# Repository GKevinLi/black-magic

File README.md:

# Black Magic: A Brushless DC Motor Driver

This is a custom 4S 20A Sensorless BLDC Motor Driver designed for drone motor operation. I haven't had time to make the drone itself because I spent all my time designing this custom PCB instead. Still worth it though.

Features a DRV8323 motor driver chip along with a STM32 microcontroller. Supports full sensorless brushless DC motor operation through PWM input along with current sensing. 

It's called Black Magic because, let's be honest here, I'm messing around with powers beyond my comprehension. I'll be lucky if this thing doesn't blow up the first time I try to plug it in, although I've done my best to make sure that doesn't happen. 20A is still way too much current for someone like me to be playing around with.

This took way longer to make than the other one.... i think its obvious why

## Features
- DRV8323 Motor Controller chip
- STM32 Microcontroller
- USB-C port for programming
- PWM Input
- BEMF Detection through a virtual neutral point
- Current Sensing capabilities
- Voltage Regulator for 3.3v power

## BOM

| Item  | Usage | Source  | Price | Quantity | LCSC ID|
| ----| ----|----|----|----|----|
| 100 uf electrolytic capaciator | Bulk Capacitance | JLCPCB | $4.65 | 20 | C7272127 |
| 10 uf capaciator | Capacitance | JLCPCB | $0.08 | 15 | C19702 |
| 3.3 nf capaciator | Capacitance | JLCPCB | $0.10 | 20 | C26404 |
| 100 nf capaciator | Capacitance | JLCPCB | $0.04 | 40 | C1525 |
| 22 uf capaciator | Bulk Capacitance | JLCPCB | $5.25 | 25 | C5189846 |
| 22 uf capaciator (0603 footprint) | Capacitance | JLCPCB | $0.09 | 10 | C59461 |
| 2.2 uf capaciator | Capacitance | JLCPCB | $0.01 | 5 | C12530 |
| 1 uf capaciator | Capacitance | JLCPCB | $0.02 | 5 | C52923 |
| 47 nf capaciator | Capacitance | JLCPCB | $0.04 | 20 | C272875 |
| Schottky Diode | Preventing reverse current | JLCPCB | $0.10 | 10 | C191023 |
| Red LED | Indication | JLCPCB | $0.03 | 5 | C2286 |
| USB C Receptacle | Programming + Power | JLCPCB | $0.30 | 6 | C2927038 |
| MOSFET | Motor Control | JLCPCB | $8.06 | 30 | C201632 |
| 10 ohm resistor | Resistance | JLCPCB | $0.02 | 30 | C25077 |
| 33k ohm resistor | Resistance | JLCPCB | $0.02 | 30 | C25779 |
| 68k ohm resistor | Resistance | JLCPCB | $0.01 | 30 | C36871 |
| 22k ohm resistor | Resistance | JLCPCB | $0.01 | 5 | C25768 |
| 100k ohm resistor | Resistance | JLCPCB | $0.01 | 5 | C25741 |
| 10k ohm resistor | Resistance | JLCPCB | $0.01 | 20 | C25741 |
| 5.1k ohm resistor | Resistance | JLCPCB | $0.01 | 15 | C25905 |
| 0.01 ohm shunt resistor | Shunt Resistance | JLCPCB | $1.05 | 19 | C393070 |
| 4.7k ohm resistor | Resistance | JLCPCB | $0.01 | 5 | C25900 |
| Button | Button | JLCPCB | $0.42 | 10 | C720477 |
| STM32 | Microcontroller | JLCPCB | $15.86 | 5 | C529355 |
| USBLC6 | USB Data Protector | JLCPCB | $0.96 | 5 | C15999 |
| TLV76133 | Voltage Regulator | JLCPCB | $1.10 | 5 | C7527500 |
| DRV8323 | Motor driver | JLCPCB | $13.29| 5 | C7527500 |
| TPS82130 | Buck Converter | JLCPCB | $6.35 | 5 | C473914 |

Total JLCPCB Assmebly Cost: $73.70

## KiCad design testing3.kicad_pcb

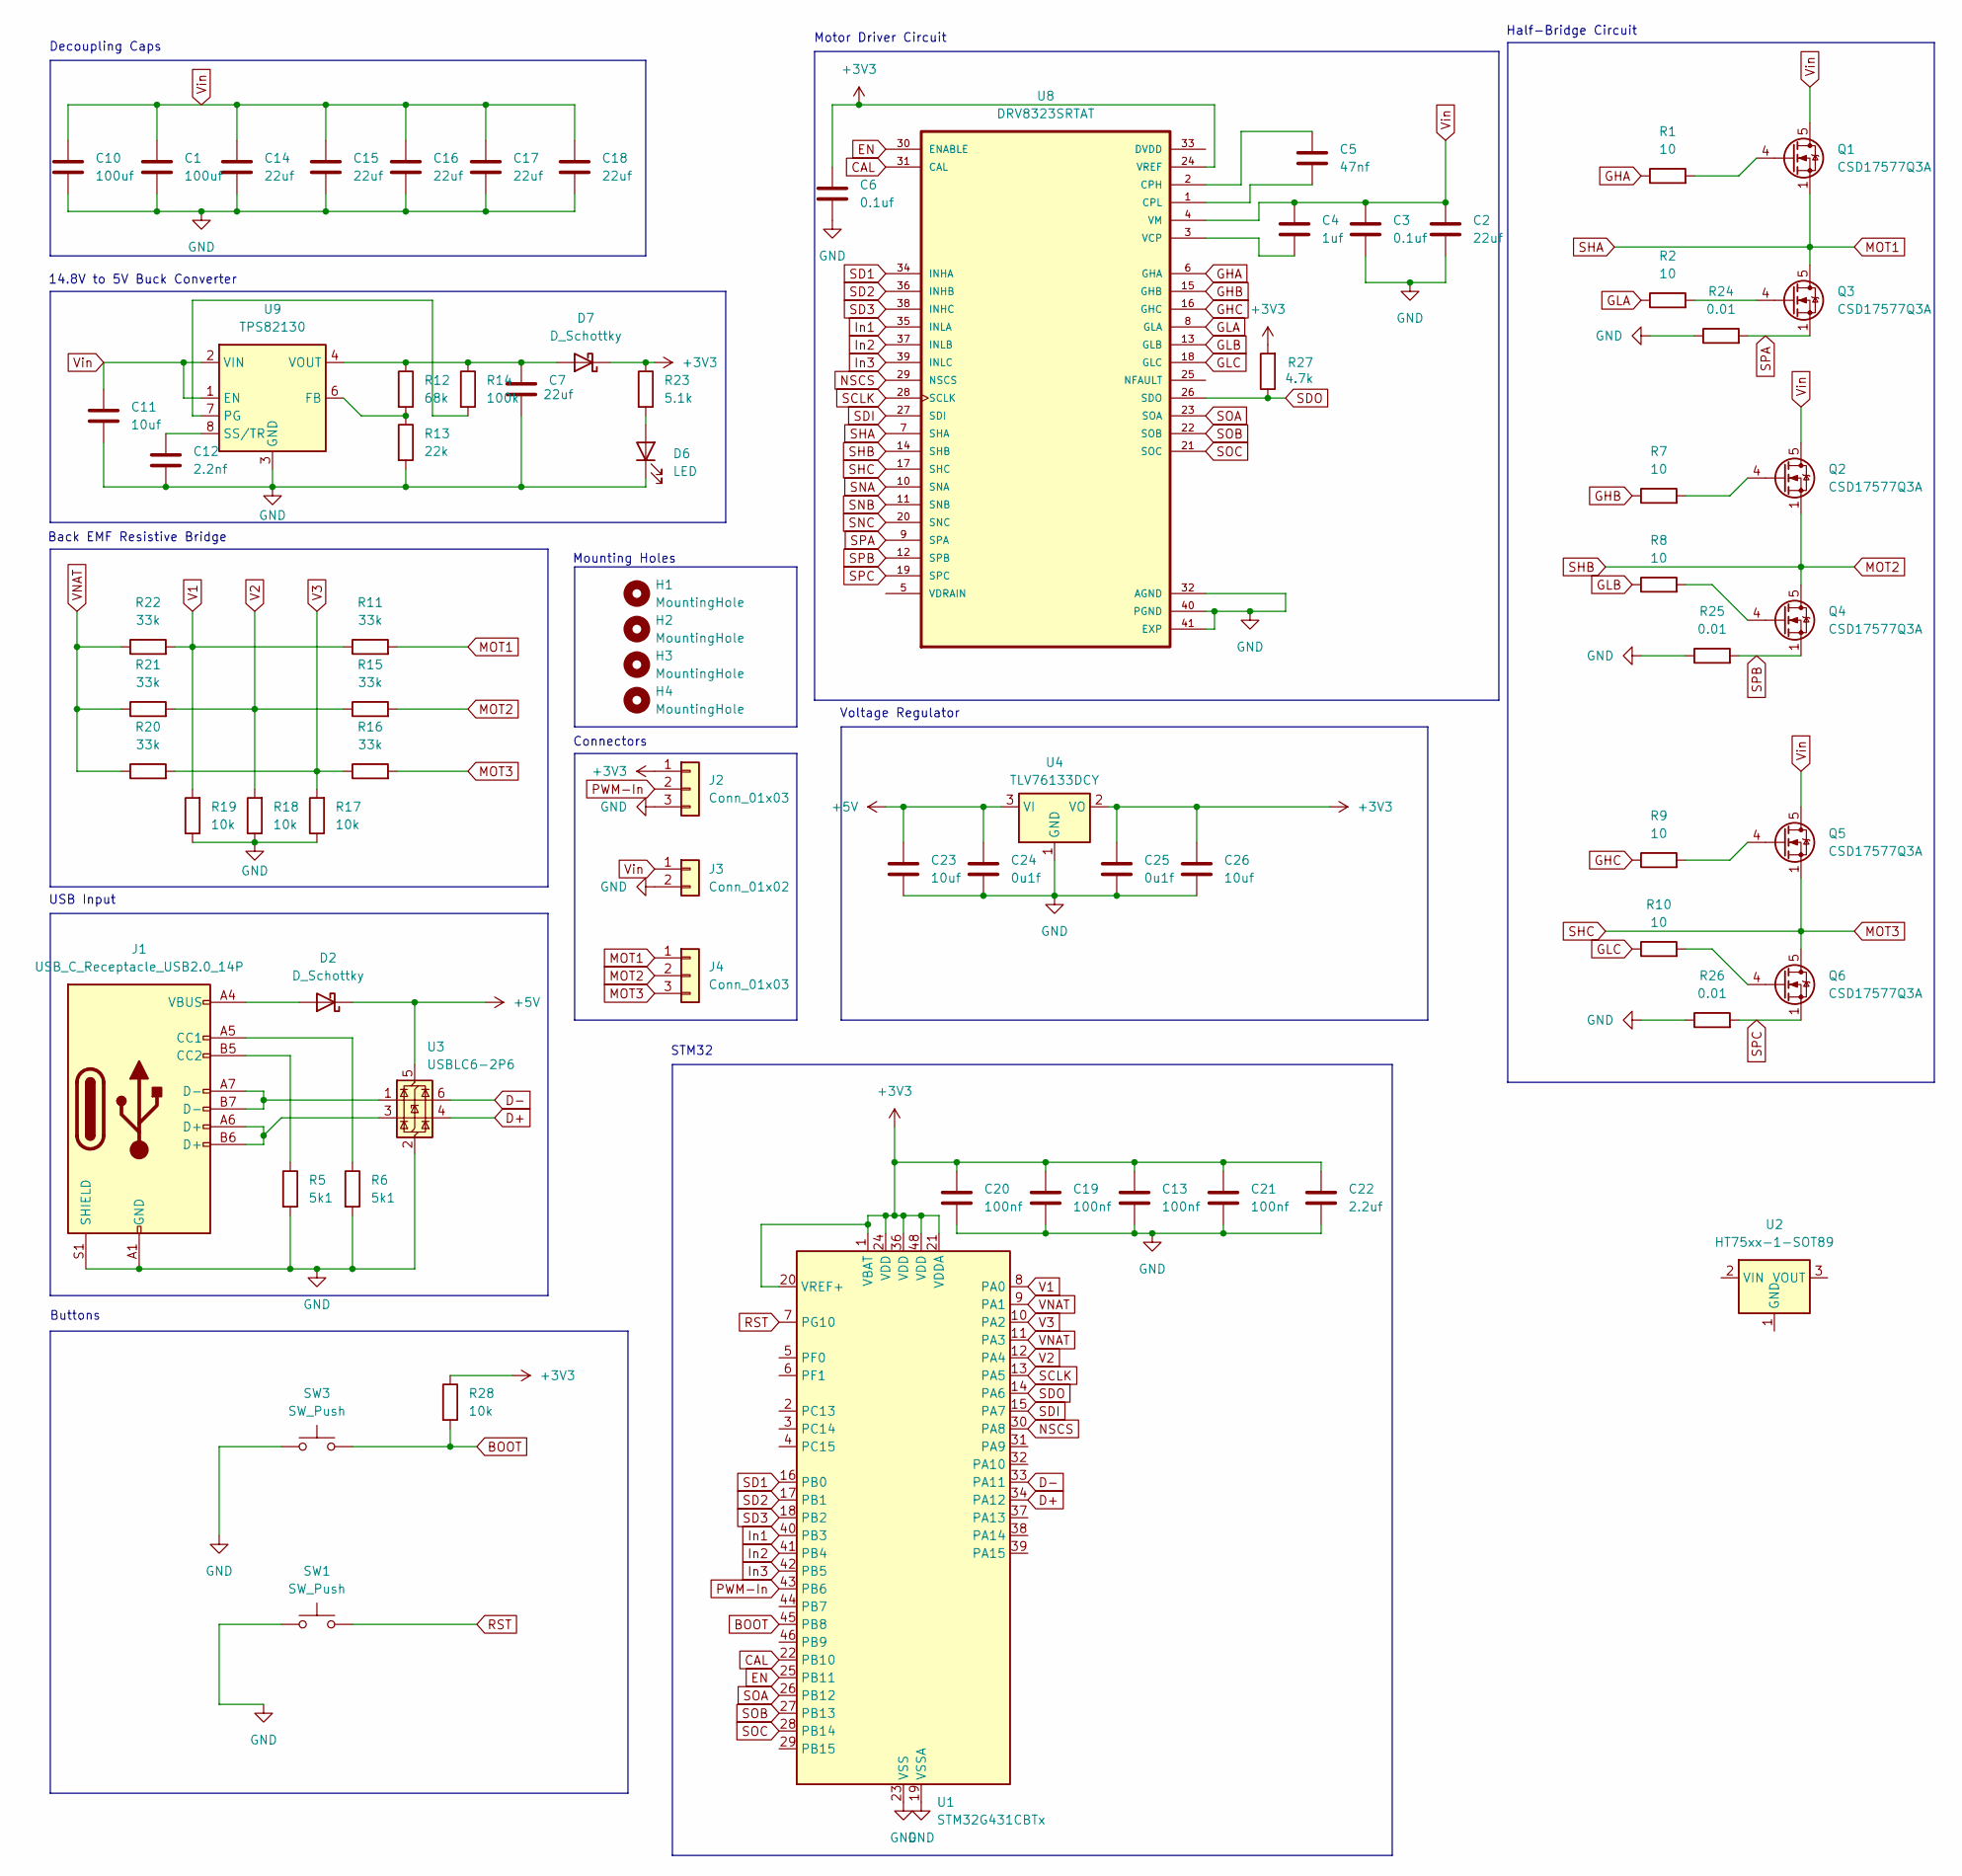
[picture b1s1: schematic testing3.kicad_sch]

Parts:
C1, C10: 100uf; CP_Elec_6.3x7.7
C2, C7: 22uf; C_0603_1608Metric
C3, C6: 0.1uf; C_0402_1005Metric
C4: 1uf; C_0402_1005Metric
C5: 47nf; C_0402_1005Metric
C11, C23, C26: 10uf; C_0603_1608Metric
C12: 2.2nf; C_0402_1005Metric
C13, C19, C20, C21: 100nf; C_0402_1005Metric
C14, C15, C16, C17, C18: 22uf; C_1812_4532Metric
C22: 2.2uf; C_0402_1005Metric
C24, C25: 0u1f; C_0402_1005Metric
D2, D7: D_Schottky; D_SOD-323
D6: LED; LED_0603_1608Metric
H1, H2, H3, H4: MountingHole; MountingHole_2.1mm
J1: USB_C_Receptacle_USB2.0_14P; USB_C_Receptacle_HCTL_HC-TYPE-C-16P-01A
J2: Conn_01x03; PinSocket_1x03_P2.54mm_Vertical
J3: Conn_01x02; SolderWire-4sqmm_1x02_P12mm_D3mm_OD6mm
J4: Conn_01x03; SolderWire-4sqmm_1x03_P12mm_D3mm_OD6mm
Q1, Q2, Q3, Q4, Q5, Q6: CSD17577Q3A; VSON-8_3.3x3.3mm_P0.65mm_NexFET
R1, R2, R7, R8, R9, R10: 10; R_0402_1005Metric
R5, R6: 5k1; R_0402_1005Metric
R11, R15, R16, R20, R21, R22: 33k; R_0402_1005Metric
R12: 68k; R_0402_1005Metric
R13: 22k; R_0402_1005Metric
R14: 100k; R_0402_1005Metric
R17, R18, R19, R28: 10k; R_0402_1005Metric
R23: 5.1k; R_0402_1005Metric
R24, R25, R26: 0.01; R_2512_6332Metric
R27: 4.7k; R_0402_1005Metric
SW1, SW3: SW_Push; SW_Push_SPST_NO_Alps_SKRK
U1: STM32G431CBTx; LQFP-48_7x7mm_P0.5mm
U2: HT75xx-1-SOT89; SOT-89-3
U3: USBLC6-2P6; SOT-666
U4: TLV76133DCY; SOT-223-3_TabPin2
U8: DRV8323SRTAT; QFN50P600X600X80-41N415X415
U9: TPS82130; Texas_SIL0008D_MicroSiP-8-1EP_2.8x3mm_P0.65mm_EP1.1x1.9mm_T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

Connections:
+3V3: C6.1, C13.1, C19.1, C20.1, C21.1, C22.1, C25.1, C26.1, D7.1 (K), J2.1, R23.1, R27.2, R28.1, U1.1 (VBAT), U1.20 (VREF+), U1.21 (VDDA), U1.24 (VDD), U1.36 (VDD), U1.48 (VDD), U4.2 (VO), U8.24 (VREF)
+5V: C23.1, C24.1, D2.1 (K), U3.5 (VBUS), U4.3 (VI)
BOOT: R28.2, SW3.2, U1.45 (PB8)
CAL: U1.22 (PB10), U8.31 (CAL)
D+: U1.34 (PA12), U3.4 (I/O2)
D-: U1.33 (PA11), U3.6 (I/O1)
EN: U1.25 (PB11), U8.30 (ENABLE)
GHA: R1.1, U8.6 (GHA)
GHB: R7.1, U8.15 (GHB)
GHC: R9.1, U8.16 (GHC)
GLA: R2.1, U8.8 (GLA)
GLB: R8.1, U8.13 (GLB)
GLC: R10.1, U8.18 (GLC)
GND: C1.2, C2.2, C3.2, C6.2, C7.2, C10.2, C11.2, C12.2, C13.2, C14.2, C15.2, C16.2, C17.2, C18.2, C19.2, C20.2, C21.2, C22.2, C23.2, C24.2, C25.2, C26.2, D6.1 (K), J1.A1 (GND), J1.A12 (GND), J1.B1 (GND), J1.B12 (GND), J1.S1 (SHIELD), J2.3, J3.2, R5.2, R6.2, R13.2, R17.1, R18.1, R19.1, R24.1, R25.1, R26.1, SW1.1, SW3.1, U1.19 (VSSA), U1.23 (VSS), U1.35 (VSS), U1.47 (VSS), U3.2 (GND), U4.1 (GND), U8.32 (AGND), U8.40 (PGND), U8.41 (EXP), U9.3 (GND), U9.9 (GND)
In1: U1.40 (PB3), U8.35 (INLA)
In2: U1.41 (PB4), U8.37 (INLB)
In3: U1.42 (PB5), U8.39 (INLC)
MOT1: J4.1, Q1.1 (S), Q1.2 (S), Q1.3 (S), Q3.5 (D), R11.2, U8.7 (SHA)
MOT2: J4.2, Q2.1 (S), Q2.2 (S), Q2.3 (S), Q4.5 (D), R15.2, U8.14 (SHB)
MOT3: J4.3, Q5.1 (S), Q5.2 (S), Q5.3 (S), Q6.5 (D), R16.2, U8.17 (SHC)
NSCS: U1.30 (PA8), U8.29 (NSCS)
unnamed: D2.2 (A), J1.A4 (VBUS), J1.A9 (VBUS), J1.B4 (VBUS), J1.B9 (VBUS)
unnamed: D6.2 (A), R23.2
unnamed: C7.1, D7.2 (A), R12.1, R14.1, U9.4 (VOUT), U9.5 (VOUT)
unnamed: J1.A5 (CC1), R6.1
unnamed: J1.B5 (CC2), R5.1
unnamed: J1.A6 (D+), J1.B6 (D+), U3.3 (I/O2)
unnamed: J1.A7 (D-), J1.B7 (D-), U3.1 (I/O1)
unnamed: Q1.4 (G), R1.2
unnamed: Q2.4 (G), R7.2
unnamed: Q3.4 (G), R2.2
unnamed: Q4.4 (G), R8.2
unnamed: Q5.4 (G), R9.2
unnamed: Q6.4 (G), R10.2
unnamed: C5.1, U8.2 (CPH)
unnamed: C5.2, U8.1 (CPL)
unnamed: C4.2, U8.3 (VCP)
unnamed: R12.2, R13.1, U9.6 (FB)
unnamed: R14.2, U9.7 (PG)
unnamed: C12.1, U9.8 (SS/TR)
PWM-In: J2.2, U1.43 (PB6)
RST: SW1.2, U1.7 (PG10)
SCLK: U1.13 (PA5), U8.28 (SCLK)
SD1: U1.16 (PB0), U8.34 (INHA)
SD2: U1.17 (PB1), U8.36 (INHB)
SD3: U1.18 (PB2), U8.38 (INHC)
SDI: U1.15 (PA7), U8.27 (SDI)
SDO: R27.1, U1.14 (PA6), U8.26 (SDO)
SNA: U8.10 (SNA)
SNB: U8.11 (SNB)
SNC: U8.20 (SNC)
SOA: U1.26 (PB12), U8.23 (SOA)
SOB: U1.27 (PB13), U8.22 (SOB)
SOC: U1.28 (PB14), U8.21 (SOC)
SPA: Q3.1 (S), Q3.2 (S), Q3.3 (S), R24.2, U8.9 (SPA)
SPB: Q4.1 (S), Q4.2 (S), Q4.3 (S), R25.2, U8.12 (SPB)
SPC: Q6.1 (S), Q6.2 (S), Q6.3 (S), R26.2, U8.19 (SPC)
V1: R11.1, R19.2, R22.2, U1.8 (PA0)
V2: R15.1, R18.2, R21.2, U1.12 (PA4)
V3: R16.1, R17.2, R20.2, U1.10 (PA2)
VNAT: R20.1, R21.1, R22.1, U1.9 (PA1), U1.11 (PA3)
Vin: C1.1, C2.1, C3.1, C4.1, C10.1, C11.1, C14.1, C15.1, C16.1, C17.1, C18.1, J3.1, Q1.5 (D), Q2.5 (D), Q5.5 (D), U8.4 (VM), U9.1 (EN), U9.2 (VIN)

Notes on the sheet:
Voltage Regulator
Decoupling Caps
Mounting Holes
USB Input
Connectors
Buttons
Back EMF Resistive Bridge
Motor Driver Circuit
STM32
14.8V to 5V Buck Converter
Half-Bridge Circuit

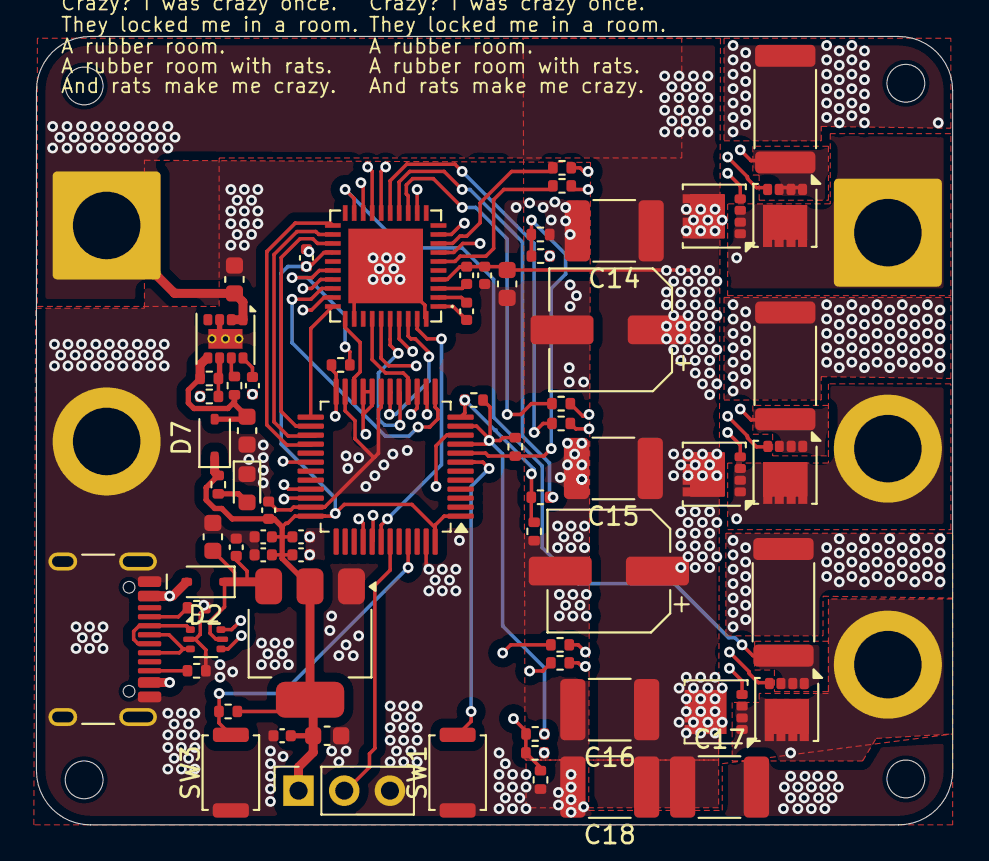
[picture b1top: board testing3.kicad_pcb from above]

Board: 4 copper layers, 50.9 x 43.8 mm, 74 parts (0 on the bottom side), 59 nets.

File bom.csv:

Designator,Footprint,Quantity,Value,LCSC Part #
"C1, C10",CP_Elec_6.3x7.7,2,100uf,
"C11, C23, C26",0603,3,10uf,
C12,0402,1,3.3nf,
"C13, C19, C20, C21",0402,4,100nf,
"C14, C15, C16, C17, C18",1812,5,22uf,
"C2, C7",0603,2,22uf,
C22,0402,1,2.2uf,
"C24, C25",0402,2,0u1f,
"C3, C6",0402,2,0.1uf,
C4,0402,1,1uf,
C5,0402,1,47nf,
"D2, D7",D_SOD-323,2,D_Schottky,
D6,0603,1,LED,
J1,USB_C_Receptacle_HCTL_HC-TYPE-C-16P-01A,1,USB_C_Receptacle_USB2.0_14P,
J2,PinSocket_1x03_P2.54mm_Vertical,1,Conn_01x03,
J3,SolderWire-4sqmm_1x02_P12mm_D3mm_OD6mm,1,Conn_01x02,
J4,SolderWire-4sqmm_1x03_P12mm_D3mm_OD6mm,1,Conn_01x03,
"Q1, Q2, Q3, Q4, Q5, Q6",VSON-8_3.3x3.3mm_P0.65mm_NexFET,6,CSD17577Q3A,
"R1, R10, R2, R7, R8, R9",0402,6,10,
"R11, R15, R16, R20, R21, R22",0402,6,33k,
R12,0402,1,68k,
R13,0402,1,22k,
R14,0402,1,100k,
"R17, R18, R19, R28",0402,4,10k,
R23,0402,1,5.1k,
"R24, R25, R26",2512,3,0.01,
R27,0402,1,4.7k,
"R5, R6",0402,2,5k1,
"SW1, SW3",SW_Push_SPST_NO_Alps_SKRK,2,SW_Push,
U1,LQFP-48_7x7mm_P0.5mm,1,STM32G431CBTx,
U3,SOT-666,1,USBLC6-2P6,
U4,SOT-223-3_TabPin2,1,TLV76133DCY,
U8,QFN50P600X600X80-41N415X415,1,DRV8323SRTAT,
U9,Texas_SIL0008D_MicroSiP-8-1EP_2.8x3mm_P0.65mm_EP1.1x1.9mm_ThermalVias,1,TPS82130,
